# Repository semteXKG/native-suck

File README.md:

# What's this about

The same thing as the SUCKer, but in native ESP IDF

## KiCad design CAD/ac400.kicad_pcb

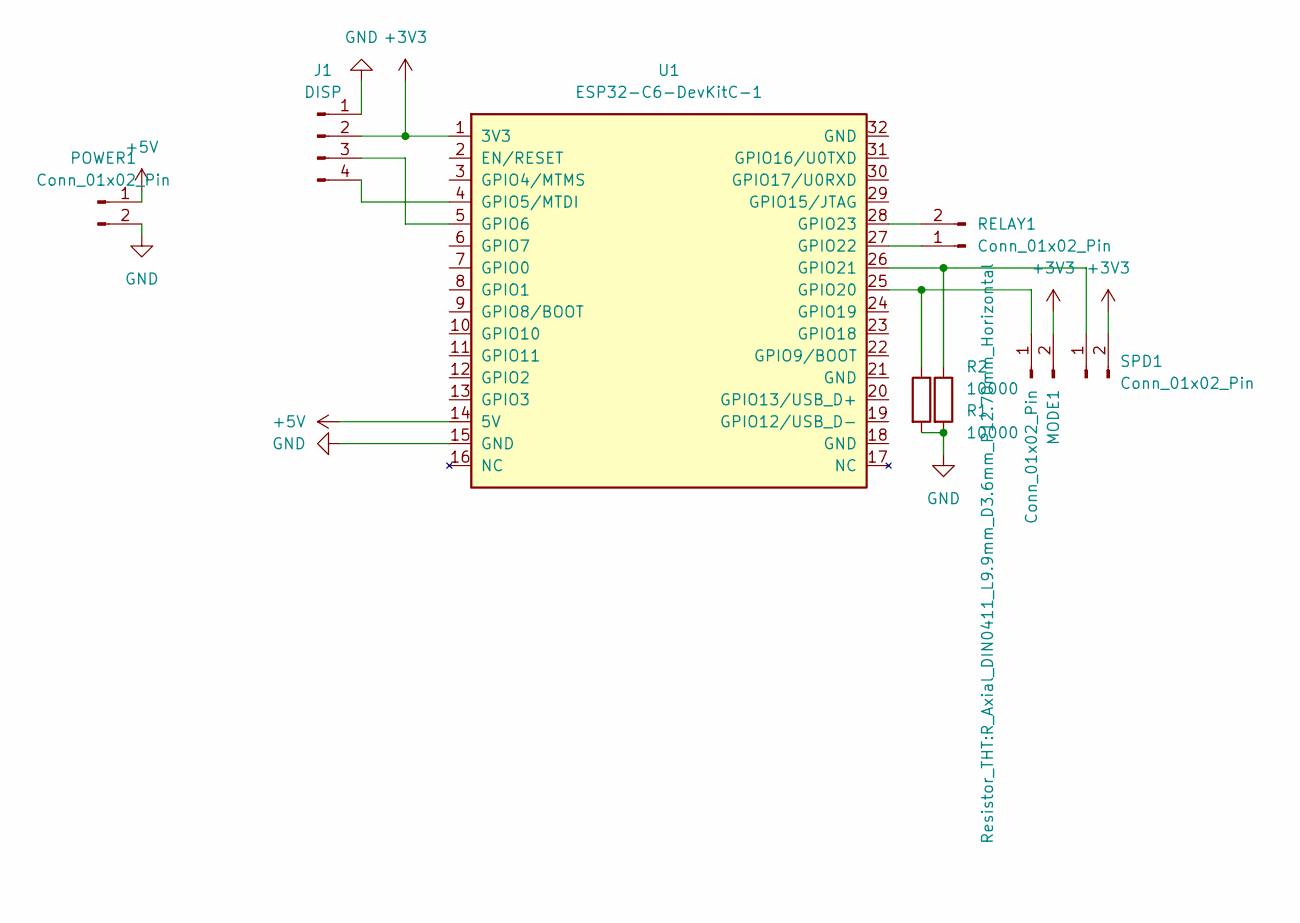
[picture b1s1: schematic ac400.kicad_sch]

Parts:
J1: DISP; JST_XH_B4B-XH-A_1x04_P2.50mm_Vertical
MODE1: Conn_01x02_Pin; JST_XH_B2B-XH-A_1x02_P2.50mm_Vertical
POWER1: Conn_01x02_Pin; JST_XH_B2B-XH-A_1x02_P2.50mm_Vertical
R1, R2: 10000; R_Axial_DIN0411_L9.9mm_D3.6mm_P12.70mm_Horizontal
RELAY1: Conn_01x02_Pin; JST_XH_B2B-XH-A_1x02_P2.50mm_Vertical
SPD1: Conn_01x02_Pin; JST_XH_B2B-XH-A_1x02_P2.50mm_Vertical
U1: ESP32-C6-DevKitC-1

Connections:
+3V3: J1.2, MODE1.2, SPD1.2, U1.1 (3V3)
+5V: POWER1.1, U1.14 (5V)
GND: J1.1, POWER1.2, R1.2, R2.2, U1.15 (GND)
unnamed: J1.3, U1.5 (GPIO6)
unnamed: J1.4, U1.4 (GPIO5/MTDI)
unnamed: MODE1.1, R1.1, U1.25 (GPIO20)
unnamed: RELAY1.1, U1.27 (GPIO22)
unnamed: RELAY1.2, U1.28 (GPIO23)
unnamed: R2.1, SPD1.1, U1.26 (GPIO21)

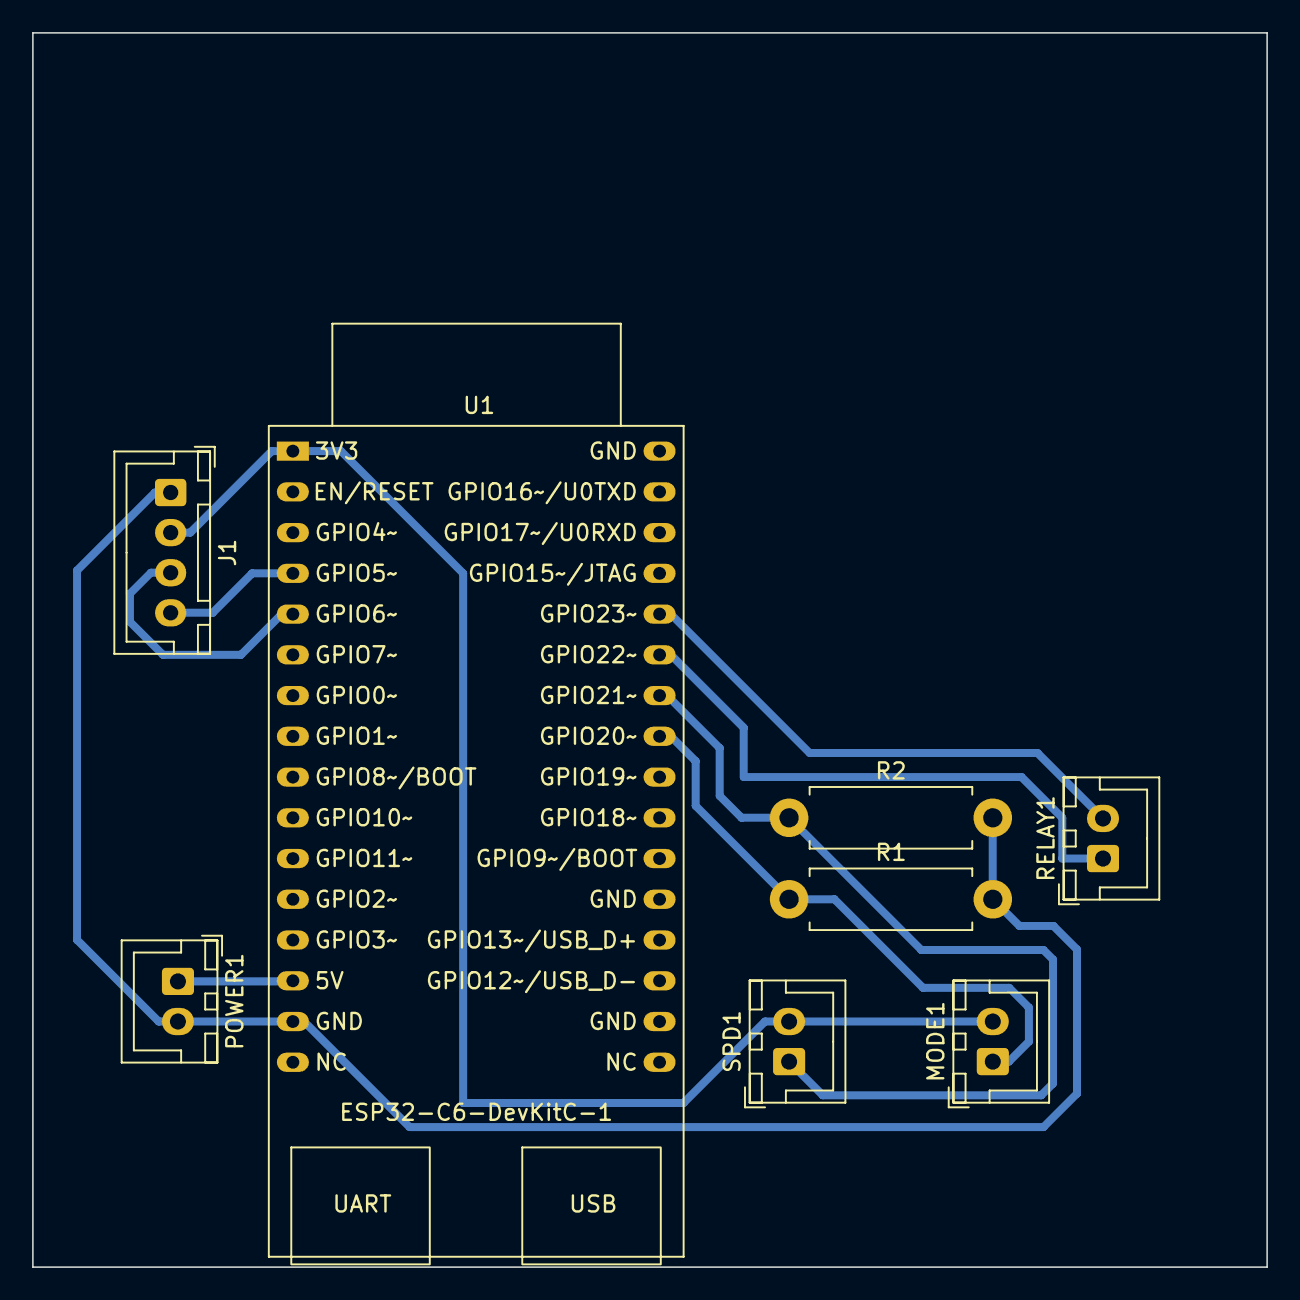
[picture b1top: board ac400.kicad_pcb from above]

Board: 2 copper layers, 76.9 x 76.9 mm, 8 parts (0 on the bottom side), 9 nets.

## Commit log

2024-02-11 native wlan and webserver
2024-02-12 added base version of webserver
2024-02-14 fixing website
2024-02-15 big time integration
2024-02-16 introducing button management and wiring everything together
2024-02-17 upgraded to 7.2, integrated nv ram store
2024-02-18 Adding ad-hoc AP
2024-02-18 adding graphical user interface
2024-02-19 adding display
2024-02-19 displaying wlan ip in display
2024-02-20 styling changes
2024-02-20 added afterrun for engine
2024-02-26 adding CAD files
2024-03-18 adding differential preasure sensor
2024-03-30 removing pres-sensors
2024-04-09 re-enabling env sensor
2024-04-21 changed to SPI display
2024-04-21 finished integration
2024-04-22 restoring last state before power loss
2024-04-22 adjusting colors
2024-05-30 Adding webserver stuff
2024-06-02 i have no idea what i'm doing
2024-06-13 implementing firmware OTA upgrades
2024-06-14 adding remote logging
2024-06-17 removing logging which caused issues
